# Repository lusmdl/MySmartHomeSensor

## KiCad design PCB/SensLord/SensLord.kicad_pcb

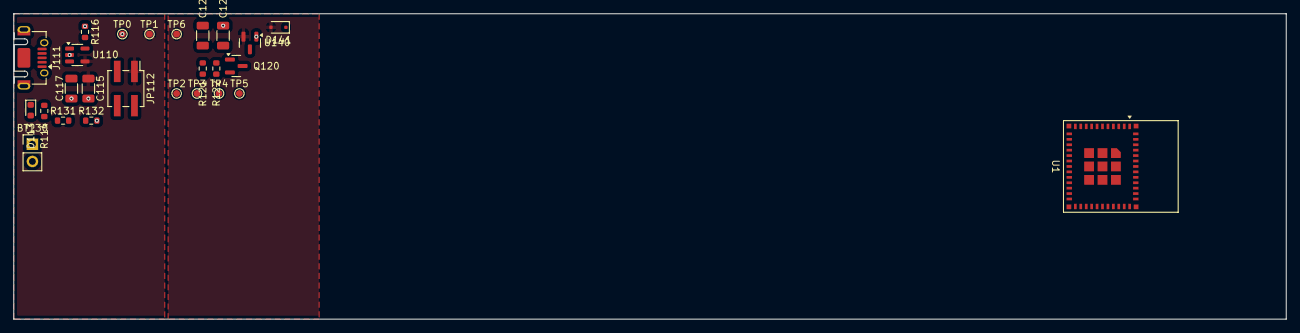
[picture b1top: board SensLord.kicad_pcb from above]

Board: 2 copper layers, 187.4 x 45.0 mm, 26 parts (0 on the bottom side), 13 nets, no tracks yet.

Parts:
BT130: Battery; PinHeader_1x02_P2.54mm_Vertical
C115, C117, C123, C124: 4.7uF; C_1206_3216Metric
D113: LED; LED_0603_1608Metric
D141: BAT54J; D_SOD-323F
J111: USB_B_Micro; USB_Micro-AB_Molex_47590-0001
JP112: Jumper_LED; PinHeader_2x02_P2.54mm_Vertical_SMD
Q120: IRLML6402; SOT-23
R114: 470; R_0603_1608Metric
R116: 2K; R_0603_1608Metric
R121: 2K2; R_0603_1608Metric
R122: 47K; R_0603_1608Metric
R131: 100k; R_0603_1608Metric
R132: 470k; R_0603_1608Metric
TP0: GND; TestPoint_Pad_D1.0mm
TP1: +5V; TestPoint_Pad_D1.0mm
TP2: +VBAT; TestPoint_Pad_D1.0mm
TP3: +BAT; TestPoint_Pad_D1.0mm
TP4: BAT_SWITCH; TestPoint_Pad_D1.0mm
TP5: BAT_ACT; TestPoint_Pad_D1.0mm
TP6: +3V3; TestPoint_Pad_D1.0mm
U1: ESP32-C6-MINI-1
U110: MCP73831-2-OT; SOT-23-5
U140: MCP1700x-330xxTT; SOT-23

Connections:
+3V3: D141.2 (A), TP6.1, U140.2 (VO)
+5V: C115.1, J111.1 (VBUS), JP112.1 (A), TP1.1, U110.4 (V_{DD})
+BAT: BT130.1 (+), C124.1, Q120.3 (D), R131.1, TP3.1, U140.3 (VI)
/BAT_ACT: R131.2, R132.1, TP5.1
/BAT_SWITCH: C123.1, Q120.1 (G), R122.1, TP4.1
GND: BT130.2 (-), C115.2, C117.2, C124.2, J111.5 (GND), R116.2, R132.2, TP0.1, U110.2 (V_{SS}), U140.1 (GND)
unnamed: D113.2 (A), JP112.2 (B)
unnamed: D113.1 (K), R114.1
unnamed: C123.2, Q120.2 (S), R121.2, R122.2
unnamed: U1.1 (GND), U1.2 (GND), U1.11 (GND), U1.14 (GND), U1.36 (GND), U1.37 (GND), U1.38 (GND), U1.39 (GND), U1.40 (GND), U1.41 (GND), U1.42 (GND), U1.43 (GND), U1.44 (GND), U1.45 (GND), U1.46 (GND), U1.47 (GND), U1.48 (GND), U1.49 (GND), U1.50 (GND), U1.51 (GND), U1.52 (GND), U1.53 (GND)
unnamed: R116.1, U110.5 (PROG)
unnamed: R114.2, U110.1 (STAT)
unnamed: C117.1, R121.1, TP2.1, U110.3 (V_{BAT})

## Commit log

2025-05-20 first steps at the scematics and pcb
2025-05-23 testing circuit ..
2025-05-23 gitignore
2025-05-23 clean
